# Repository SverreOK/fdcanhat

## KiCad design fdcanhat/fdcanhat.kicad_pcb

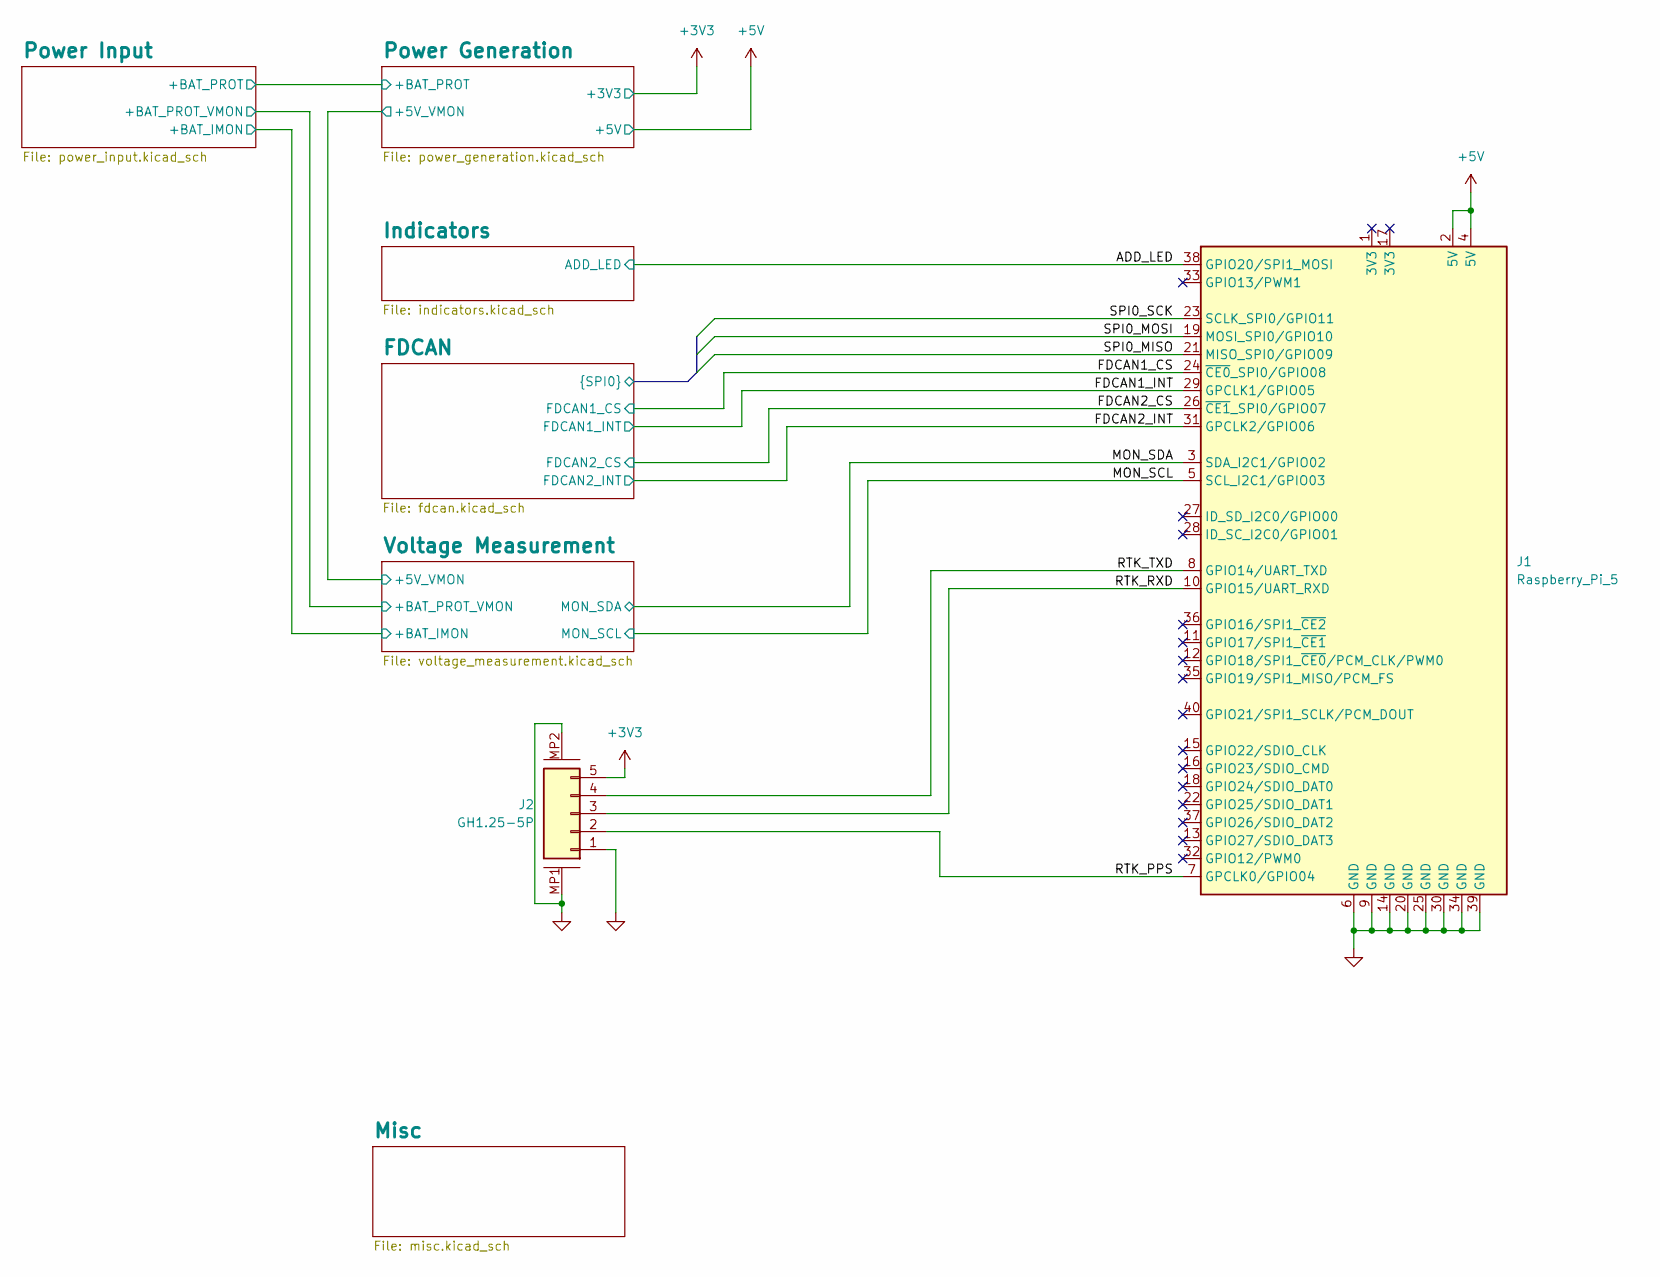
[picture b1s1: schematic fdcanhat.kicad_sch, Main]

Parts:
J1: Raspberry_Pi_5; PinHeader_2x20_P2.54mm_Vertical
J2: GH1.25-5P; SM05B-GHS-TB-LF-SN; LCSC C189896

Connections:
+3V3: J2.5; also elsewhere on the board
+5V: J1.2 (5V), J1.4 (5V); also elsewhere on the board
/ADD_LED: J1.38 (GPIO20/SPI1_MOSI); also elsewhere on the board
/FDCAN1_CS: J1.24 (~CE0_SPI0/GPIO08); also elsewhere on the board
/FDCAN1_INT: J1.29 (GPCLK1/GPIO05); also elsewhere on the board
/FDCAN2_CS: J1.26 (~CE1_SPI0/GPIO07); also elsewhere on the board
/FDCAN2_INT: J1.31 (GPCLK2/GPIO06); also elsewhere on the board
/FDCAN/SPI0_MISO: J1.21 (MISO_SPI0/GPIO09); also elsewhere on the board
/FDCAN/SPI0_MOSI: J1.19 (MOSI_SPI0/GPIO10); also elsewhere on the board
/FDCAN/SPI0_SCK: J1.23 (SCLK_SPI0/GPIO11); also elsewhere on the board
/MON_SCL: J1.5 (SCL_I2C1/GPIO03); also elsewhere on the board
/MON_SDA: J1.3 (SDA_I2C1/GPIO02); also elsewhere on the board
/RTK_PPS: J1.7 (GPCLK0/GPIO04), J2.2
/RTK_RXD: J1.10 (GPIO15/UART_RXD), J2.3
/RTK_TXD: J1.8 (GPIO14/UART_TXD), J2.4
GND: J1.6 (GND), J1.9 (GND), J1.14 (GND), J1.20 (GND), J1.25 (GND), J1.30 (GND), J1.34 (GND), J1.39 (GND), J2.1, J2.MP1, J2.MP2; also elsewhere on the board

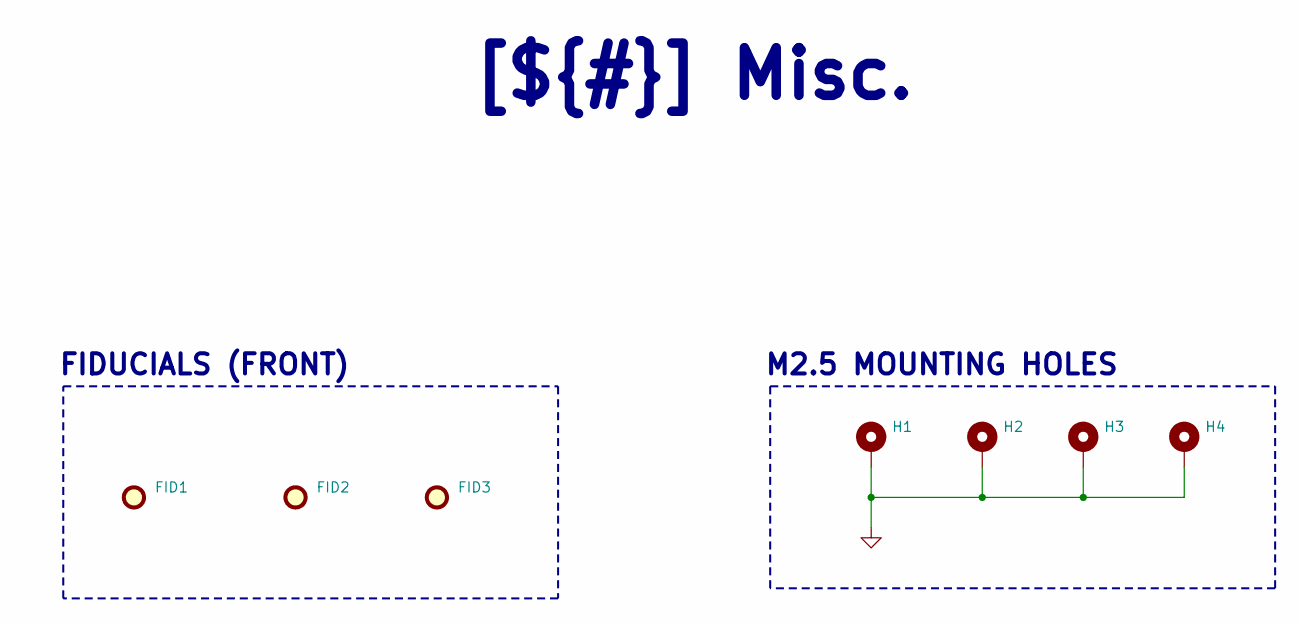
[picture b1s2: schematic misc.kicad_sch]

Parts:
FID1, FID2, FID3: Fiducial; Fiducial_1mm_Mask2mm
H1, H2, H3, H4: MountingHole_Pad; MountingHole_2.7mm_M2.5_Pad_Via

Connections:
GND: H1.1, H2.1, H3.1, H4.1; also elsewhere on the board

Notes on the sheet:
FIDUCIALS (FRONT)
M2.5 MOUNTING HOLES
[${#}] ${TITLE}

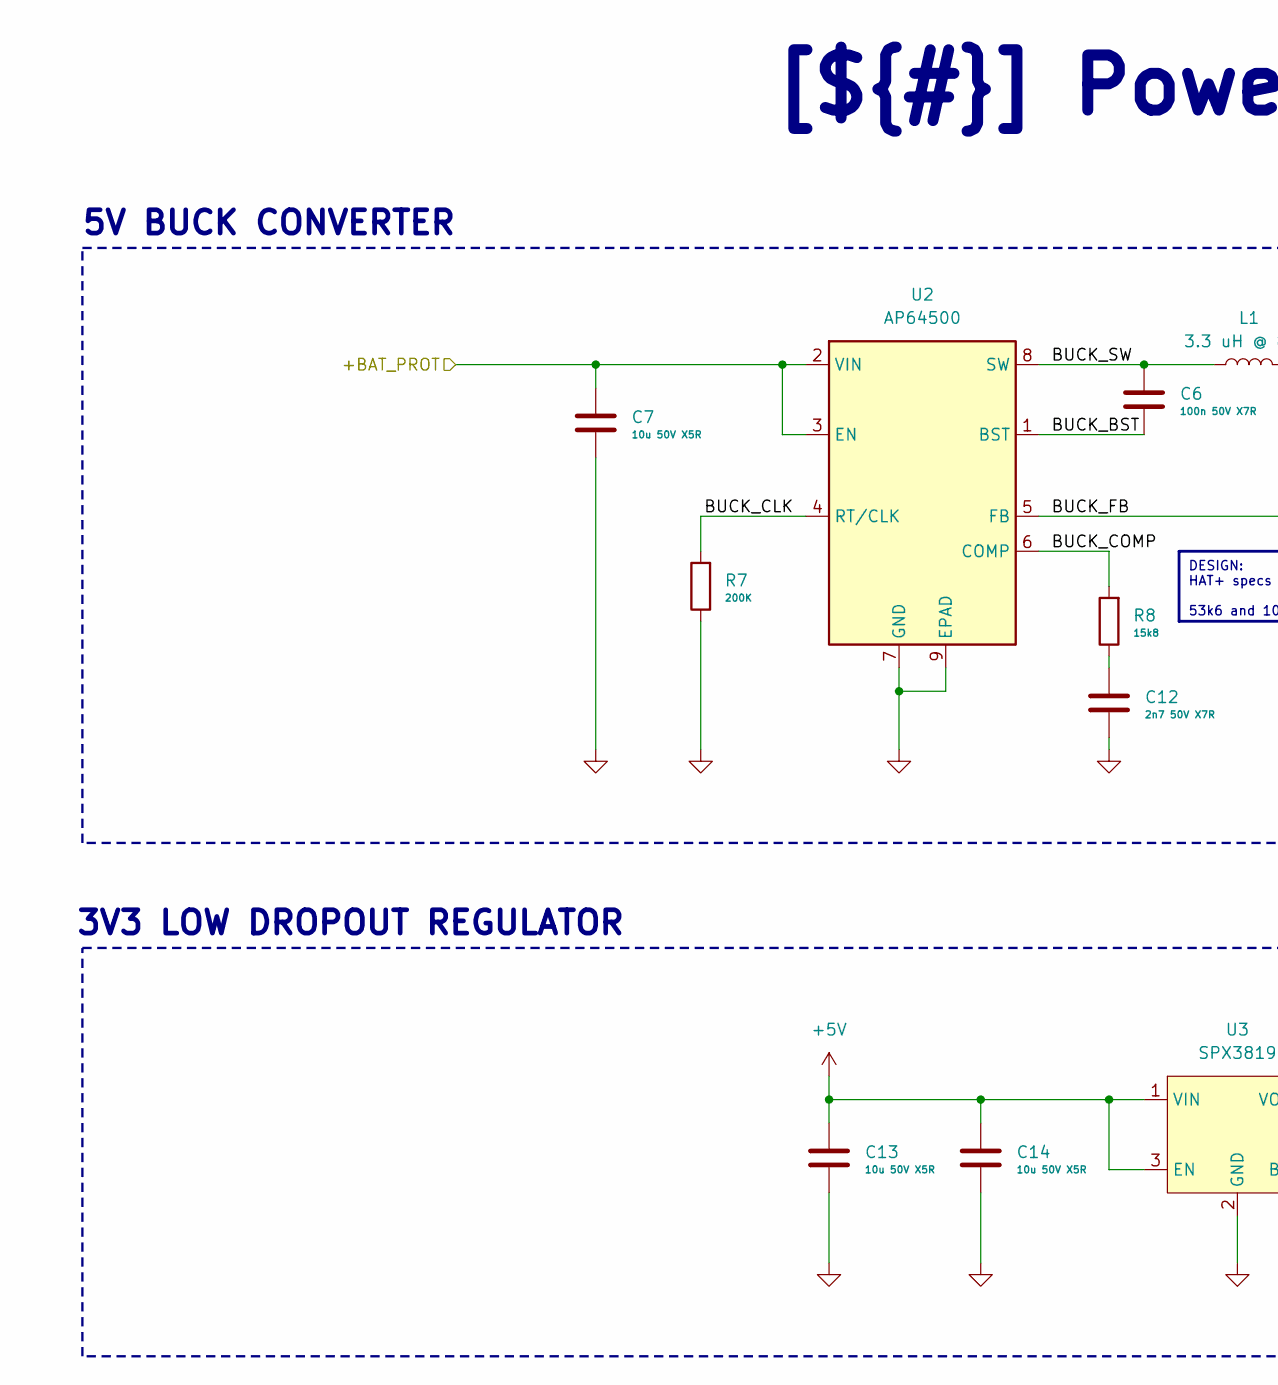
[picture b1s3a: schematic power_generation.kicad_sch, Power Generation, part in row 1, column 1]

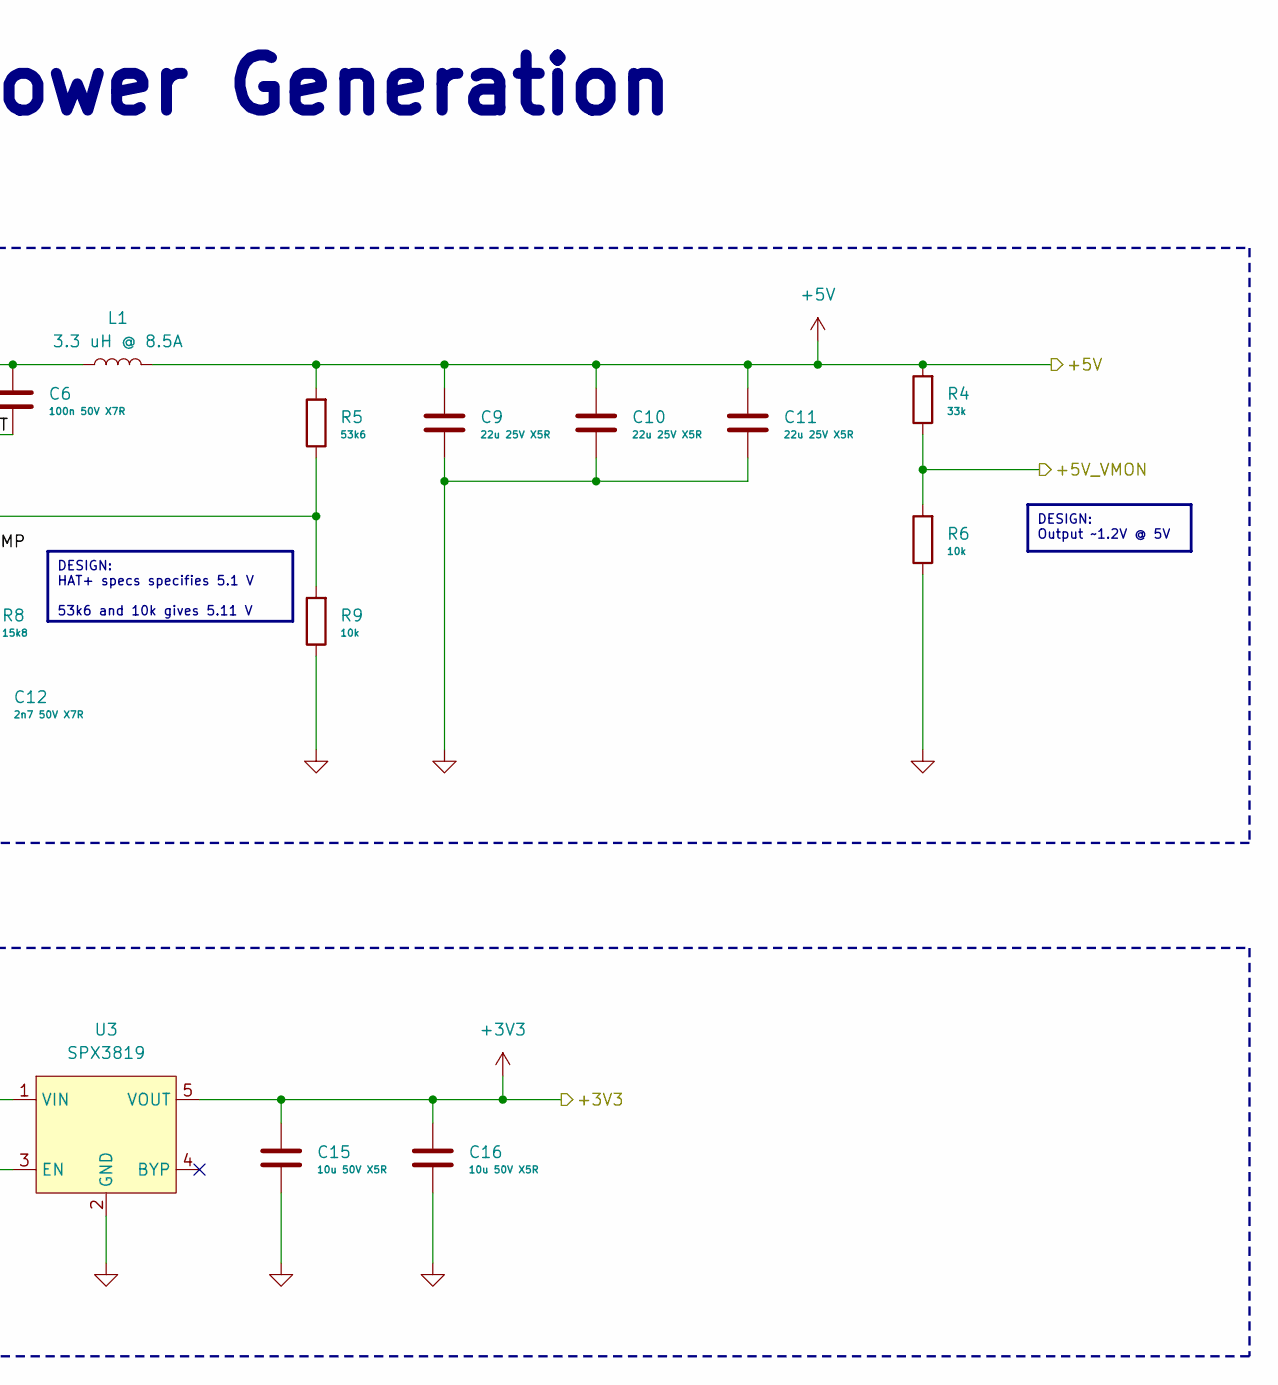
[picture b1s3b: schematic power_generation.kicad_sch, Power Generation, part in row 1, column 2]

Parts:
C6: 100n 50V X7R; C_0402_1005Metric; LCSC C307331
C7, C13, C14, C15, C16: 10u 50V X5R; C_0805_2012Metric; LCSC C440198
C9, C10, C11: 22u 25V X5R; C_0805_2012Metric; LCSC C45783
C12: 2n7 50V X7R; C_0402_1005Metric; LCSC C106251
L1: 3.3 uH @ 8.5A; IND-SMD_L7.0-W6.6; LCSC C167219
R4: 33k; R_0402_1005Metric; LCSC C25779
R5: 53k6; R_0402_1005Metric; LCSC C53398
R6, R9: 10k; R_0402_1005Metric; LCSC C25744
R7: 200K; R_0402_1005Metric; LCSC C25764
R8: 15k8; R_0402_1005Metric; LCSC C26956
U2: AP64500; SO-8-EP; LCSC C2070920
U3: SPX3819; SOT-23-5; LCSC C9055

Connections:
+3V3: C15.1, C16.1, U3.5 (VOUT); also elsewhere on the board
+5V: C9.1, C10.1, C11.1, C13.1, C14.1, L1.2, R4.2, R5.2, U3.1 (VIN), U3.3 (EN); also elsewhere on the board
+BAT_PROT: C7.1, U2.2 (VIN), U2.3 (EN); also elsewhere on the board
/Power Generation/+5V_VMON: R4.1, R6.2; also elsewhere on the board
/Power Generation/BUCK_BST: C6.2, U2.1 (BST)
/Power Generation/BUCK_CLK: R7.2, U2.4 (RT/CLK)
/Power Generation/BUCK_COMP: R8.2, U2.6 (COMP)
/Power Generation/BUCK_FB: R5.1, R9.2, U2.5 (FB)
/Power Generation/BUCK_SW: C6.1, L1.1, U2.8 (SW)
GND: C7.2, C9.2, C10.2, C11.2, C12.2, C13.2, C14.2, C15.2, C16.2, R6.1, R7.1, R9.1, U2.7 (GND), U2.9 (EPAD), U3.2 (GND); also elsewhere on the board
unnamed: C12.1, R8.1

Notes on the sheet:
3V3 LOW DROPOUT REGULATOR
5V BUCK CONVERTER
DESIGN: Output ~1.2V @ 5V
[${#}] ${TITLE}
DESIGN: HAT+ specs specifies 5.1 V 53k6 and 10k gives 5.11 V

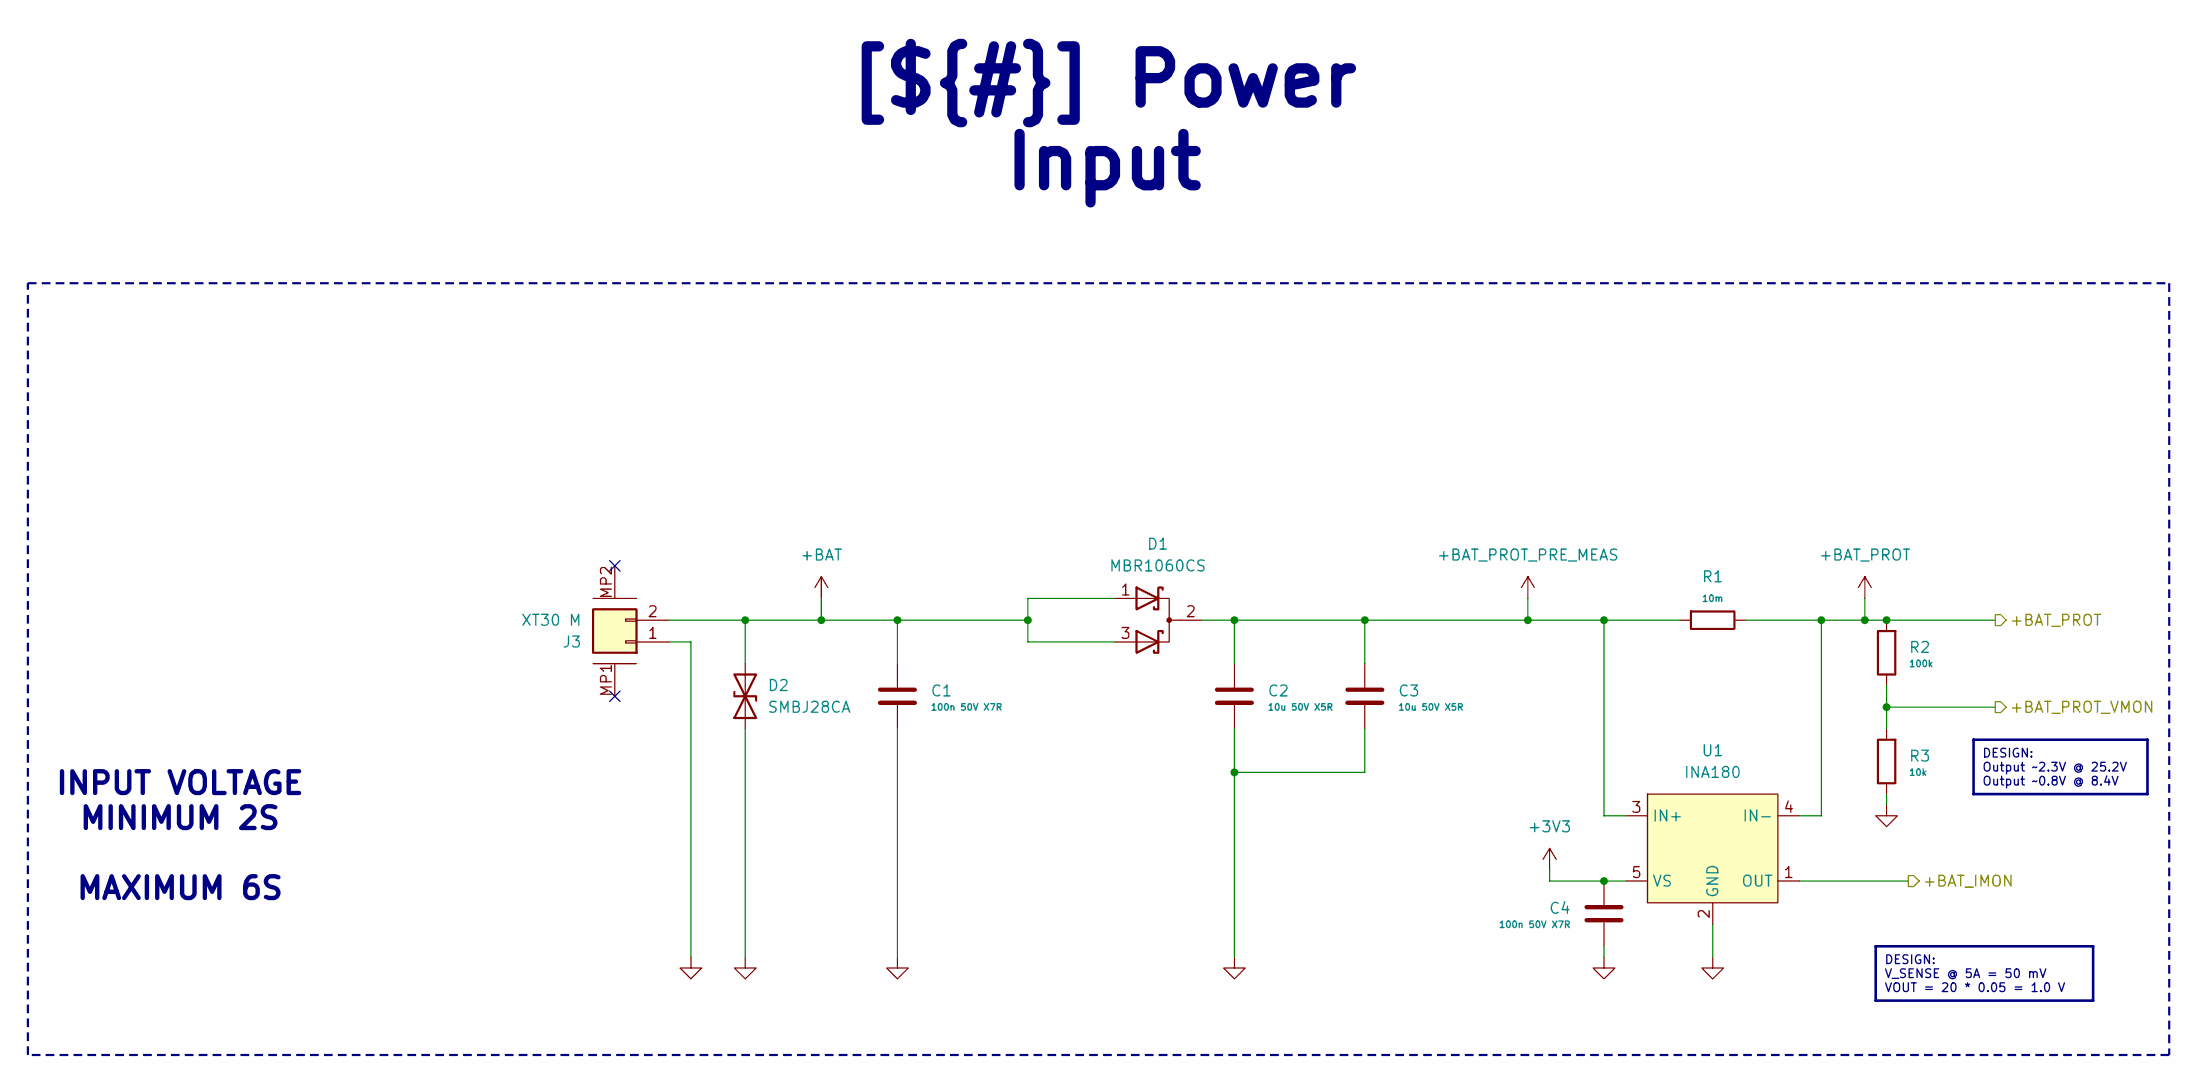
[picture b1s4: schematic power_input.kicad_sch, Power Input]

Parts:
C1, C4: 100n 50V X7R; C_0402_1005Metric; LCSC C307331
C2, C3: 10u 50V X5R; C_0805_2012Metric; LCSC C440198
D1: MBR1060CS; TO-252-2_L6.6-W6.1-P4.57-LS10.2-TR-CW; LCSC C5220847
D2: SMBJ28CA; D_SMB; LCSC C19077583
J3: XT30 M; XT30PW-M
R1: 10m; R_2512_6332Metric; LCSC C108943
R2: 100k; R_0402_1005Metric; LCSC C25741
R3: 10k; R_0402_1005Metric; LCSC C25744
U1: INA180; SOT-23-5; LCSC C122228

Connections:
+3V3: C4.2, U1.5 (VS); also elsewhere on the board
+BAT: C1.1, D1.1 (A), D1.3 (A), D2.2 (A2), J3.2
+BAT_PROT: R1.1, R2.2, U1.4 (IN-); also elsewhere on the board
+BAT_PROT_PRE_MEAS: C2.1, C3.1, D1.2 (K), R1.2, U1.3 (IN+)
/Power Input/+BAT_IMON: U1.1 (OUT); also elsewhere on the board
/Power Input/+BAT_PROT_VMON: R2.1, R3.2; also elsewhere on the board
GND: C1.2, C2.2, C3.2, C4.1, D2.1 (A1), J3.1, R3.1, U1.2 (GND); also elsewhere on the board

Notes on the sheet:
INPUT VOLTAGE MINIMUM 2S MAXIMUM 6S
DESIGN: Output ~2.3V @ 25.2V Output ~0.8V @ 8.4V
[${#}] ${TITLE}
DESIGN: V_SENSE @ 5A = 50 mV VOUT = 20 * 0.05 = 1.0 V

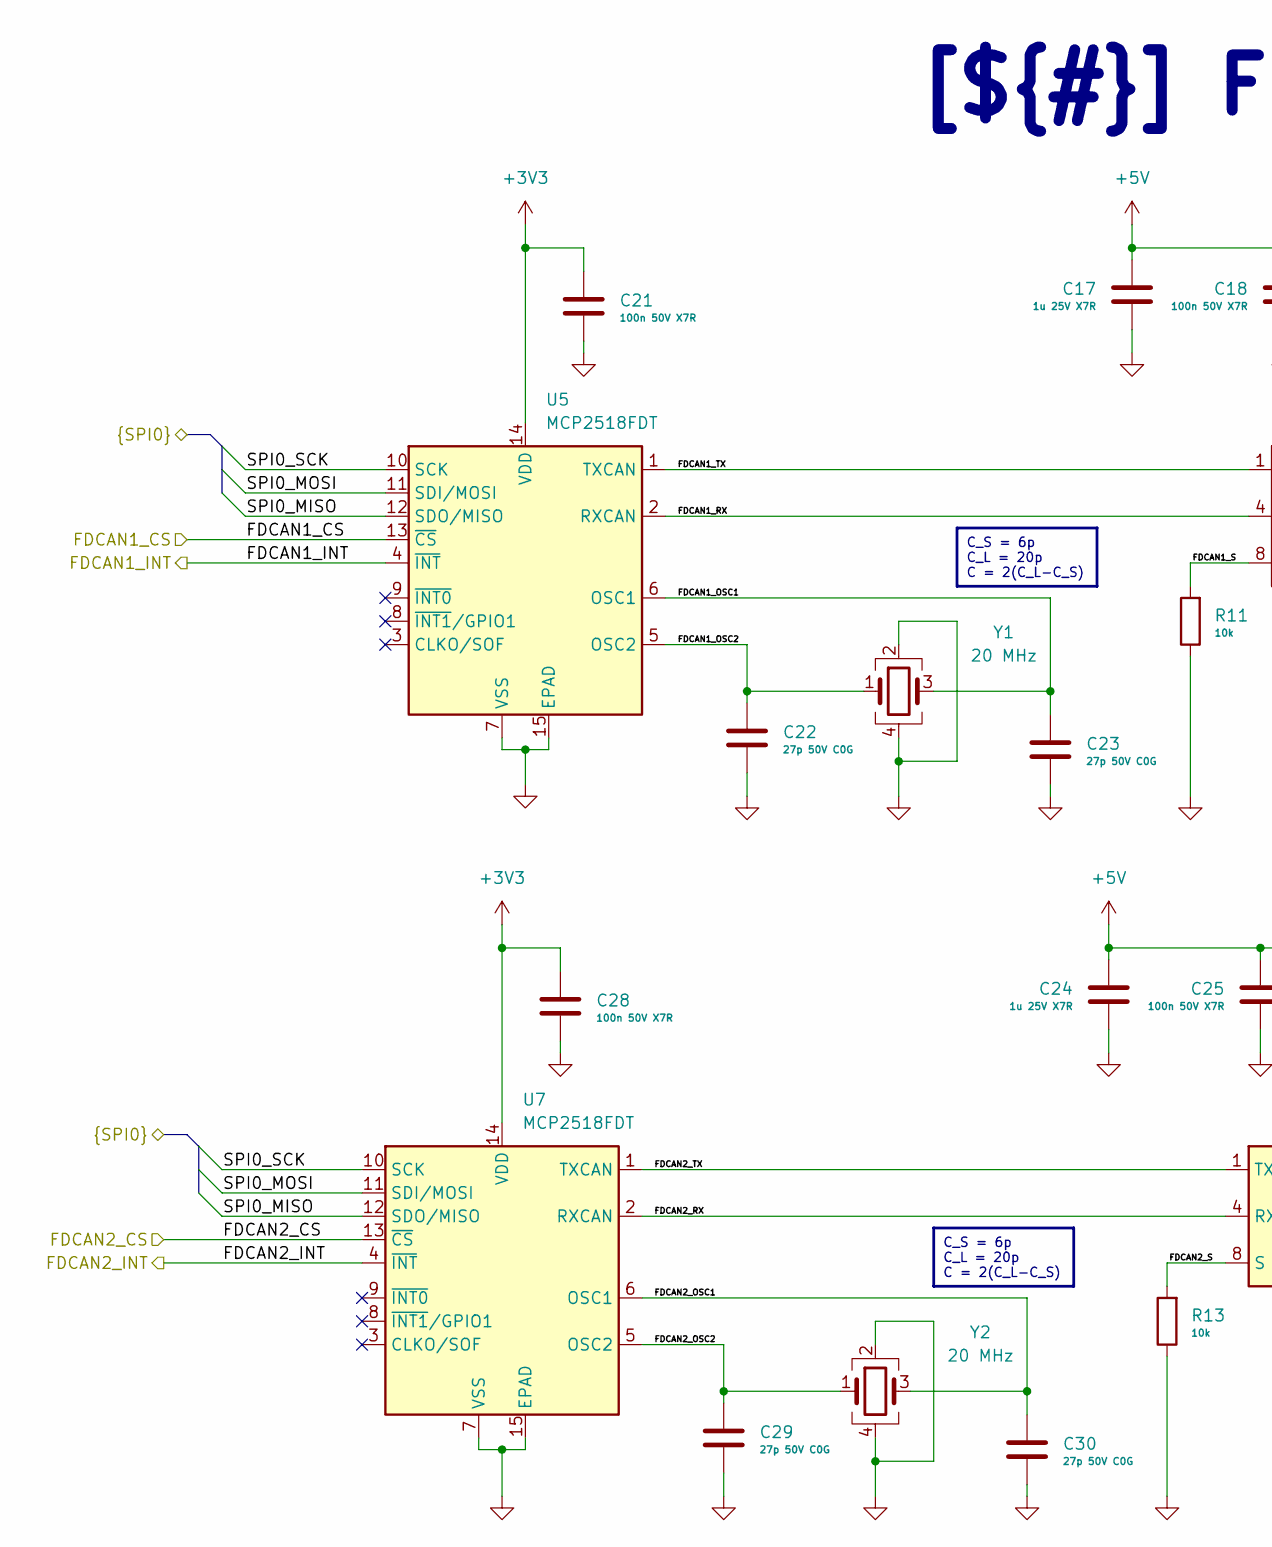
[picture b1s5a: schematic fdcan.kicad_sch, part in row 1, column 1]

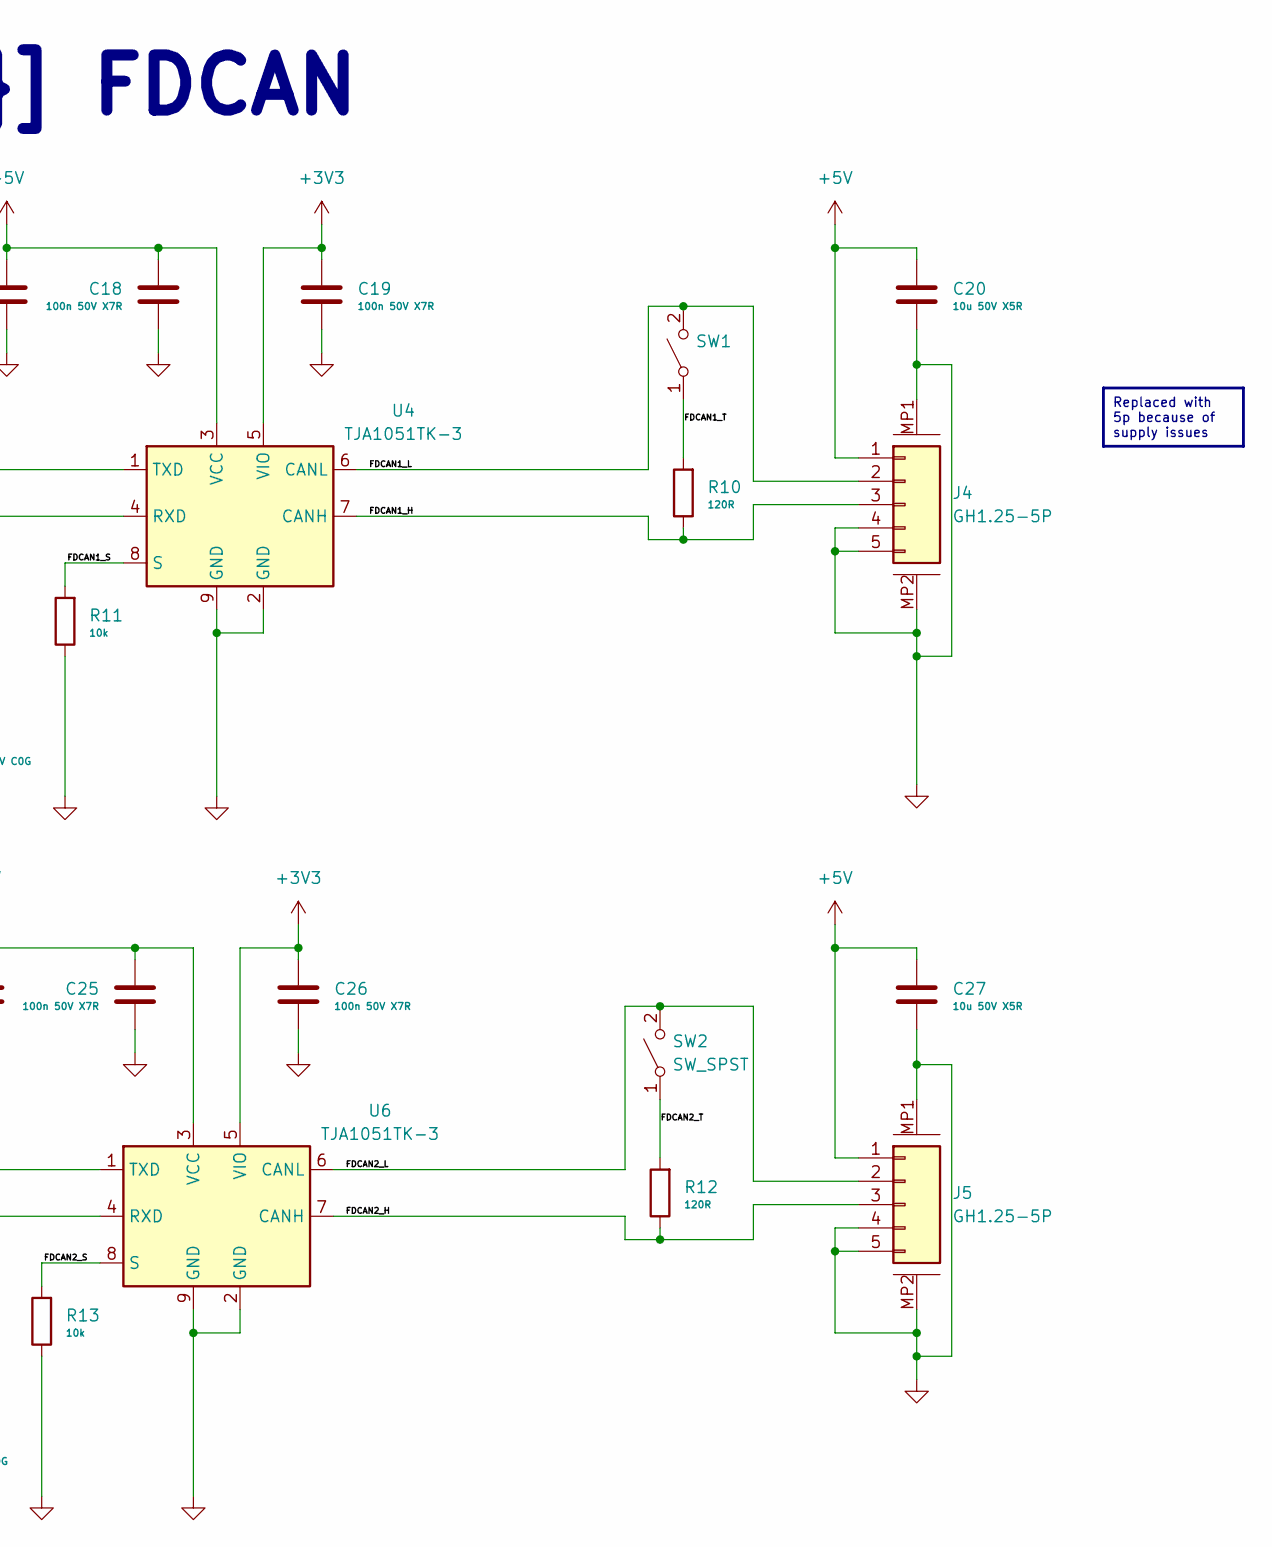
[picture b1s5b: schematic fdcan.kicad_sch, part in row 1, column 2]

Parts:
C17, C24: 1u 25V X7R; C_0402_1005Metric; LCSC C52923
C18, C19, C21, C25, C26, C28: 100n 50V X7R; C_0402_1005Metric; LCSC C307331
C20, C27: 10u 50V X5R; C_0805_2012Metric; LCSC C440198
C22, C23, C29, C30: 27p 50V C0G; C_0402_1005Metric; LCSC C3889037
J4, J5: GH1.25-5P; SM05B-GHS-TB-LF-SN; LCSC C189896
R10, R12: 120R; R_0805_2012Metric; LCSC C17437
R11, R13: 10k; R_0402_1005Metric; LCSC C25744
SW1, SW2: SW_SPST; SW-SMD_DSIC01LSGET; LCSC C54948
U4, U6: TJA1051TK-3; HVSON-8-1EP_3x3mm_P0.65mm_EP1.6x2.4mm; LCSC C2875699
U5, U7: MCP2518FDT; DFN-14-1EP_3x4.5mm_P0.65mm_EP1.65x4.25mm; LCSC C621395
Y1, Y2: 20 MHz; CRYSTAL-SMD_4P-L3.2-W2.5-BL-2; LCSC C9004

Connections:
+3V3: C19.1, C21.1, C26.1, C28.1, U4.5 (VIO), U5.14 (VDD), U6.5 (VIO), U7.14 (VDD); also elsewhere on the board
+5V: C17.1, C18.1, C20.1, C24.1, C25.1, C27.1, J4.1, J5.1, U4.3 (VCC), U6.3 (VCC); also elsewhere on the board
/FDCAN1_CS: U5.13 (~CS); also elsewhere on the board
/FDCAN1_INT: U5.4 (~INT); also elsewhere on the board
/FDCAN2_CS: U7.13 (~CS); also elsewhere on the board
/FDCAN2_INT: U7.4 (~INT); also elsewhere on the board
/FDCAN/FDCAN1_H: J4.3, R10.1, U4.7 (CANH)
/FDCAN/FDCAN1_L: J4.2, SW1.2 (B), U4.6 (CANL)
/FDCAN/FDCAN1_OSC1: C23.1, U5.6 (OSC1), Y1.3
/FDCAN/FDCAN1_OSC2: C22.1, U5.5 (OSC2), Y1.1
/FDCAN/FDCAN1_RX: U4.4 (RXD), U5.2 (RXCAN)
/FDCAN/FDCAN1_S: R11.2, U4.8 (S)
/FDCAN/FDCAN1_T: R10.2, SW1.1 (A)
/FDCAN/FDCAN1_TX: U4.1 (TXD), U5.1 (TXCAN)
/FDCAN/FDCAN2_H: J5.3, R12.1, U6.7 (CANH)
/FDCAN/FDCAN2_L: J5.2, SW2.2 (B), U6.6 (CANL)
/FDCAN/FDCAN2_OSC1: C30.1, U7.6 (OSC1), Y2.3
/FDCAN/FDCAN2_OSC2: C29.1, U7.5 (OSC2), Y2.1
/FDCAN/FDCAN2_RX: U6.4 (RXD), U7.2 (RXCAN)
/FDCAN/FDCAN2_S: R13.2, U6.8 (S)
/FDCAN/FDCAN2_T: R12.2, SW2.1 (A)
/FDCAN/FDCAN2_TX: U6.1 (TXD), U7.1 (TXCAN)
/FDCAN/SPI0_MISO: U5.12 (SDO/MISO), U7.12 (SDO/MISO); also elsewhere on the board
/FDCAN/SPI0_MOSI: U5.11 (SDI/MOSI), U7.11 (SDI/MOSI); also elsewhere on the board
/FDCAN/SPI0_SCK: U5.10 (SCK), U7.10 (SCK); also elsewhere on the board
GND: C17.2, C18.2, C19.2, C20.2, C21.2, C22.2, C23.2, C24.2, C25.2, C26.2, C27.2, C28.2, C29.2, C30.2, J4.4, J4.5, J4.MP1, J4.MP2, J5.4, J5.5, J5.MP1, J5.MP2, R11.1, R13.1, U4.2 (GND), U4.9 (GND), U5.7 (VSS), U5.15 (EPAD), U6.2 (GND), U6.9 (GND), U7.7 (VSS), U7.15 (EPAD), Y1.2, Y1.4, Y2.2, Y2.4; also elsewhere on the board

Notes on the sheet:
C_S = 6p C_L = 20p C = 2(C_L-C_S)
Replaced with 5p because of supply issues
[${#}] ${TITLE}

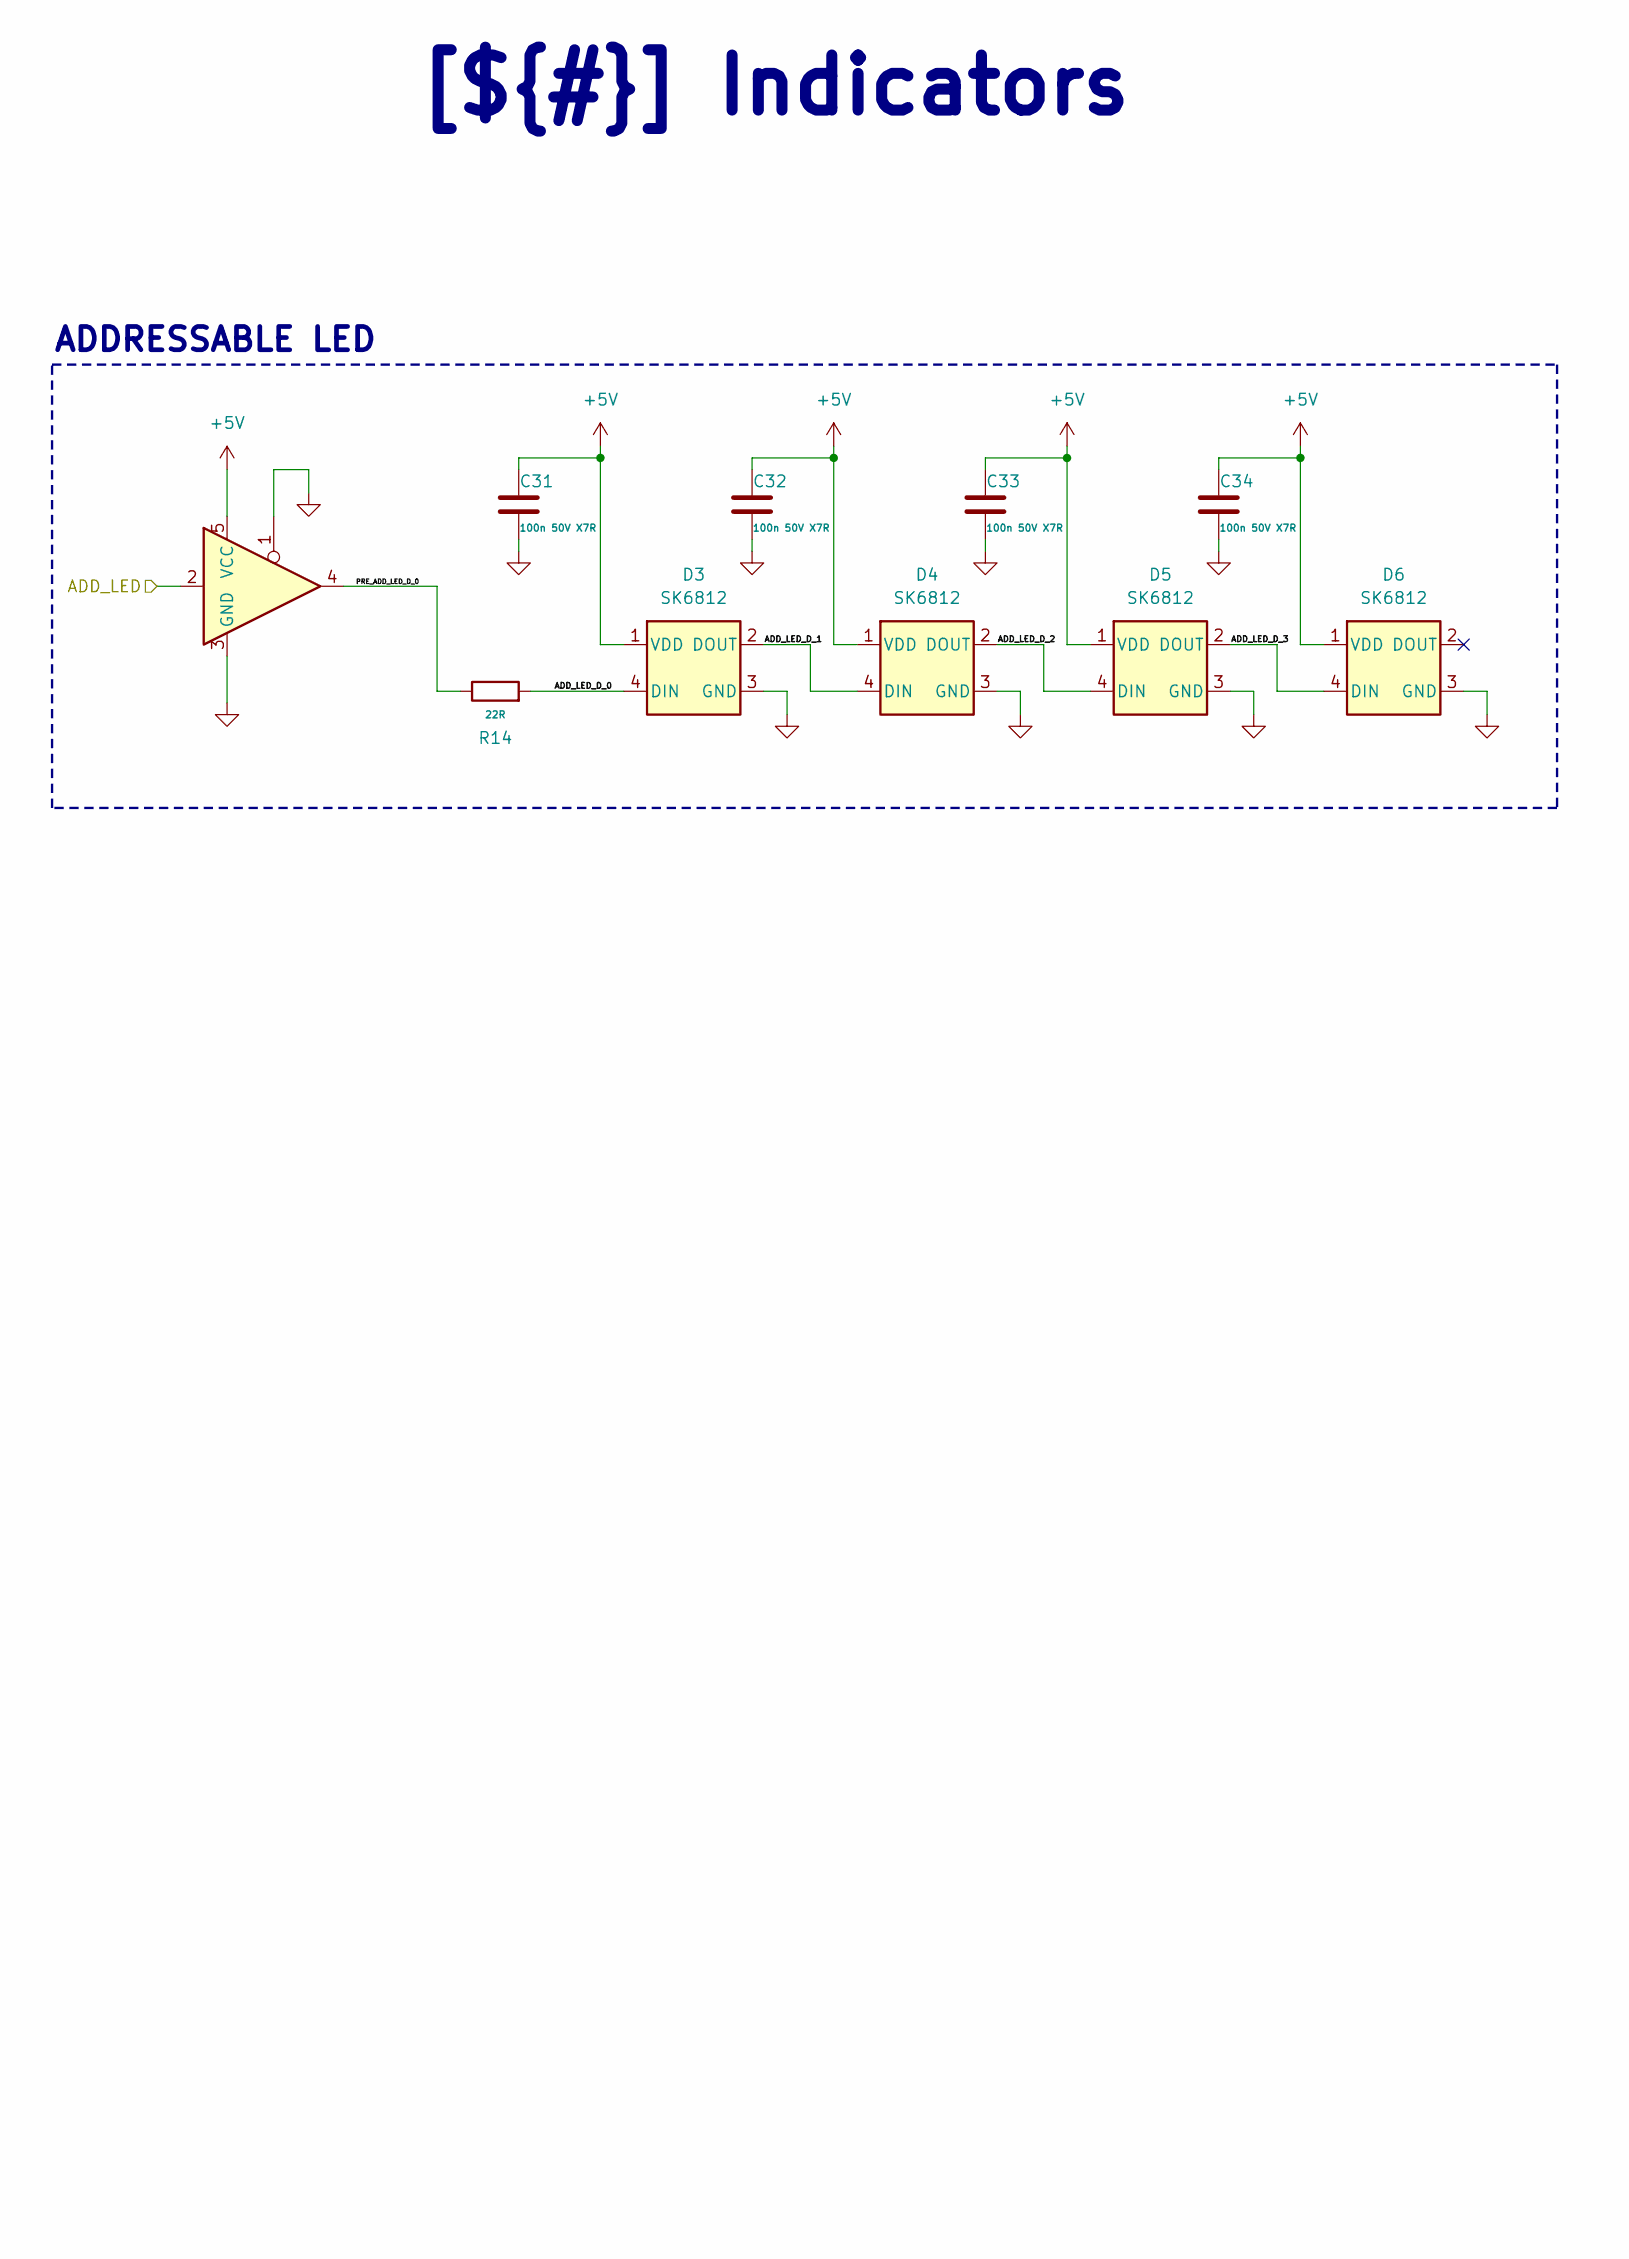
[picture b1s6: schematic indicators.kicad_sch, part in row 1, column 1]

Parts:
C31, C32, C33, C34: 100n 50V X7R; C_0402_1005Metric; LCSC C307331
D3, D4, D5, D6: SK6812; LED-SMD_4P-L2.0-W2.0-BR; LCSC C2909058
R14: 22R; R_0402_1005Metric; LCSC C25092
U8: 74AHCT1G125; SOT-23-5; LCSC C20617903

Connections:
+5V: C31.1, C32.1, C33.1, C34.1, D3.1 (VDD), D4.1 (VDD), D5.1 (VDD), D6.1 (VDD), U8.5 (VCC); also elsewhere on the board
/ADD_LED: U8.2; also elsewhere on the board
/Indicators/ADD_LED_D_0: D3.4 (DIN), R14.2
/Indicators/ADD_LED_D_1: D3.2 (DOUT), D4.4 (DIN)
/Indicators/ADD_LED_D_2: D4.2 (DOUT), D5.4 (DIN)
/Indicators/ADD_LED_D_3: D5.2 (DOUT), D6.4 (DIN)
/Indicators/PRE_ADD_LED_D_0: R14.1, U8.4
GND: C31.2, C32.2, C33.2, C34.2, D3.3 (GND), D4.3 (GND), D5.3 (GND), D6.3 (GND), U8.1, U8.3 (GND); also elsewhere on the board

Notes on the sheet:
ADDRESSABLE LED
[${#}] ${TITLE}

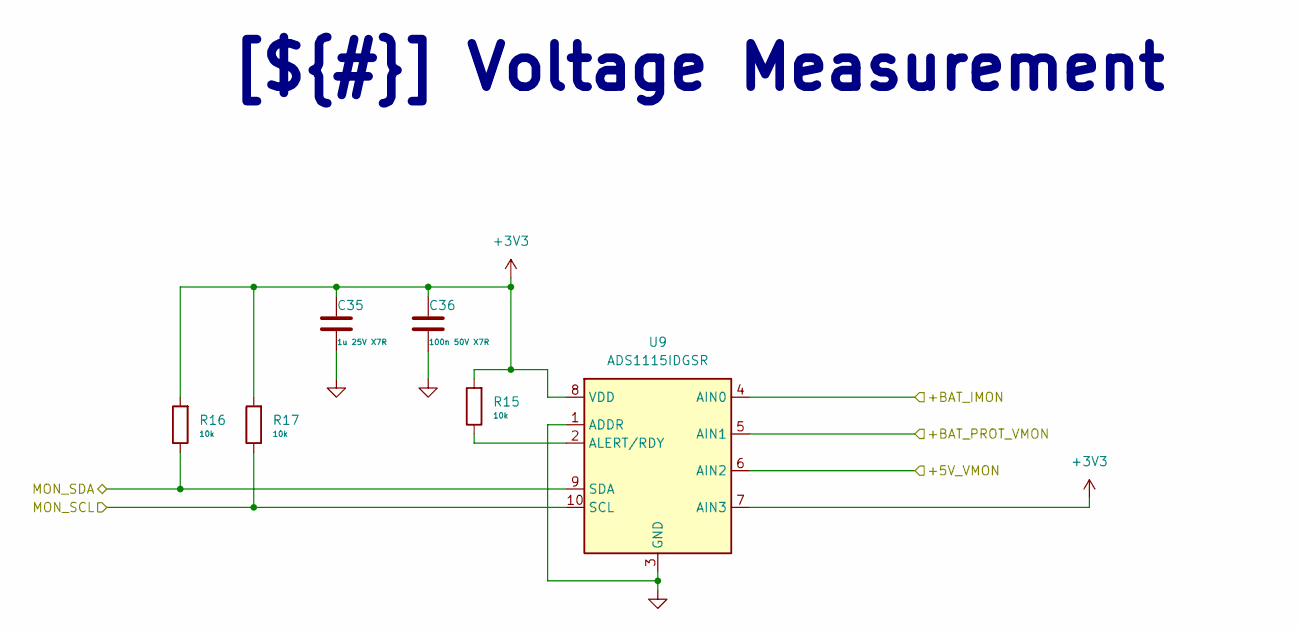
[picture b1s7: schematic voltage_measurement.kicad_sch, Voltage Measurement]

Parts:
C35: 1u 25V X7R; C_0402_1005Metric; LCSC C52923
C36: 100n 50V X7R; C_0402_1005Metric; LCSC C307331
R15, R16, R17: 10k; R_0402_1005Metric; LCSC C25744
U9: ADS1115IDGSR; VSSOP-10_3x3mm_P0.5mm; LCSC C37593

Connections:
+3V3: C35.1, C36.1, R15.2, R16.2, R17.2, U9.7 (AIN3), U9.8 (VDD); also elsewhere on the board
/MON_SCL: R17.1, U9.10 (SCL); also elsewhere on the board
/MON_SDA: R16.1, U9.9 (SDA); also elsewhere on the board
/Power Generation/+5V_VMON: U9.6 (AIN2); also elsewhere on the board
/Power Input/+BAT_IMON: U9.4 (AIN0); also elsewhere on the board
/Power Input/+BAT_PROT_VMON: U9.5 (AIN1); also elsewhere on the board
GND: C35.2, C36.2, U9.1 (ADDR), U9.3 (GND); also elsewhere on the board
unnamed: R15.1, U9.2 (ALERT/RDY)

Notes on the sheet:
[${#}] ${TITLE}
